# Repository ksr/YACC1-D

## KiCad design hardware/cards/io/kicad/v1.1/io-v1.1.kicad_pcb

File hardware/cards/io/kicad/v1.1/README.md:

# io-v1.1 — KiCad conversion

Generated 2026-09-23 by `tools/eagle_to_kicad_all.py` from the Eagle design `IO V1.1` in `hardware/cards/io/eagle/v1.1/`. **The Eagle files are the record of what was designed and built; this KiCad project is derived from them and is regenerated from scratch on every run of the tool** (hand edits here will be lost - once a card is edited in KiCad, remove it from the tool's list). This revision was FABRICATED (see `hardware/FABRICATED.md`).

## Files

| File | What it is |
|---|---|
| `io-v1.1.kicad_pro` | project; OSH Park rules (6 mil track, 5 mil clearance, 10 mil drill, 4 mil annular) |
| `io-v1.1.kicad_sch` | root sheet; 6 sub-sheet(s) `io-v1.1-sheetN.kicad_sch` mirror the Eagle sheets |
| `io-v1.1-eagle.kicad_sym` | project symbol library generated from the Eagle libraries used (units = Eagle gates) |
| `io-v1.1.kicad_pcb` | the board: 2 copper layers, 71 footprints, 1409 track segments, 158 vias |
| `io-v1.1-eagle.pretty/` | project footprint library extracted from the imported board |
| `reports/` | ERC (`erc.json`), DRC (`drc.json`), schematic PDF, board renders (`-top.png`, `-bottom.png`), netlist + `netlist-compare.txt` |

## Proof

Schematic-vs-board netlist comparison (`tools/kicad/compare_netlists.py`: every (reference, pad) partition must be identical): **MATCH (104/104 nets)**

```
  same connectivity, different net name: [('/Sheet 2/ICLK', 'ICLK'), ('/Sheet 2/RX', 'RX'), ('/Sheet 2/RX-IN', 'RX-IN'), ('/Sheet 2/TX-OUT', 'TX-OUT'), ('/Sheet 5/-IO-ADDRSEL', '-IO-ADDRSEL'), ('/Sheet 5/-IO-DATASEL', '-IO-DATASEL'), ('/Sheet 5/-IO-SEL0', '-IO-SEL0'), ('/Sheet 5/-IO-SEL1', '-IO-SEL1'), ('/Sheet 5/-IO-SEL2', '-IO-SEL2'), ('/Sheet 5/-IO-SEL3', '-IO-SEL3'), ('/Sheet 5/-IO-SEL4', '-IO-SEL4'), ('/Sheet 5/-IO-SEL5', '-IO-SEL5'), ('/Sheet 5/-IO-SEL6', '-IO-SEL6'), ('/Sheet 5/-IO-SEL7', '-IO-SEL7'), ('Net-(HI0A-D0)', 'N$70'), ('Net-(HI0A-D1)', 'N$69'), ('Net-(HI0A-D2)', 'N$68'), ('Net-(HI0A-D3)', 'N$28'), ('Net-(IC1-INT)', 'N$57'), ('Net-(IC1-TX)', 'N$37'), ('Net-(IC1-XTAL1)', 'N$31'), ('Net-(IC2-C1+)', 'N$63'), ('Net-(IC2-C1-)', 'N$62'), ('Net-(IC2-C2+)', 'N$52'), ('Net-(IC2-C2-)', 'N$51'), ('Net-(IC2-V+)', 'N$64'), ('Net-(IC2-V-)', 'N$65'), ('Net-(IC3A-A1)', 'N$1'), ('Net-(IC3A-A2)', 'N$2'), ('Net-(IC3A-A3)', 'N$3'), ('Net-(IC3A-A4)', 'N$4'), ('Net-(IC3A-G)', 'N$32'), ('Net-(IC3B-A1)', 'N$5'), ('Net-(IC3B-A2)', 'N$6'), ('Net-(IC3B-A3)', 'N$7'), ('Net-(IC3B-A4)', 'N$8'), ('Net-(IC4-CLK)', 'N$41'), ('Net-(IC4-Q1)', 'N$26'), ('Net-(IC4-Q2)', 'N$25'), ('Net-(IC4-Q3)', 'N$24'), ('Net-(IC4-Q4)', 'N$23'), ('Net-(IC4-Q5)', 'N$22'), ('Net-(IC4-Q6)', 'N$21'), ('Net-(IC4-Q7)', 'N$20'), ('Net-(IC4-Q8)', 'N$19'), ('Net-(IC5-G1)', 'N$29'), ('Net-(IC5-G2A)', 'N$27'), ('Net-(IC6C-O)', 'N$33'), ('Net-(IC7A-O)', 'N$30'), ('Net-(IC7B-I0)', 'N$67'), ('Net-(IC8F-I)', 'N$66'), ('Net-(IC9-Q1)', 'N$74'), ('Net-(IC9-Q2)', 'N$73'), ('Net-(IC9-Q3)', 'N$72'), ('Net-(IC9-Q4)', 'N$71'), ('Net-(IC10-CLK)', 'N$40'), ('Net-(IC11A-O)', 'N$75'), ('Net-(IN0-P)', 'N$34'), ('Net-(J1-Pad2)', 'N$35'), ('Net-(J1-Pad3)', 'N$36'), ('Net-(OUT0-PadA)', 'N$9'), ('Net-(PWR0-PadA)', 'N$11'), ('Net-(R3-Pad1)', 'N$14'), ('Net-(R4-Pad1)', 'N$15'), ('Net-(R5-Pad1)', 'N$10'), ('Net-(R6-Pad1)', 'N$12'), ('Net-(R7-Pad1)', 'N$13'), ('Net-(R8-Pad1)', 'N$16'), ('Net-(R9-Pad1)', 'N$18'), ('Net-(R10-Pad1)', 'N$17'), ('Net-(TM1-S)', 'N$44')]
```

## Readability

`tools/kicad/sch_overlaps.py` over every sheet: text over text 13, text over a symbol body 57, text crossed by a line 22, items off the drawing frame or on the title block 0. What is left is mostly the Eagle drawing itself (parts placed that close in Eagle) or KiCad drawing pin numbers centred on short pins.

## Residual ERC / DRC

ERC by type: endpoint_off_grid 38, isolated_pin_label 66, pin_not_connected 8, pin_not_driven 1, unconnected_wire_endpoint 17.
`isolated_pin_label` = the converter's per-net global labels (cosmetic); `power_pin_not_driven` / unused-unit notes are the same ones KiCad's own Eagle importer leaves. `unconnected_wire_endpoint` / `pin_not_connected` = wire stubs Eagle leaves bare (mostly net wires ending on a bus, which is drawn as graphics here); since 2026-09-23 the converter no longer hangs a label on every such end (that was most of the label clutter), so they show as KiCad warnings.

DRC by type: items_not_allowed 22, lib_footprint_mismatch 2, silk_edge_clearance 4, silk_over_copper 199, silk_overlap 60, text_height 4, text_thickness 1; unconnected items 0; schematic parity 0.
Silk-over-pad and clearance notes reflect the Eagle design as drawn; unconnected items are Eagle airwires (parts the design left unrouted).

Converter: converted: 214 symbols, 595 wires, 204 labels, 103 junctions, 8 bus lines, 17 no-connects

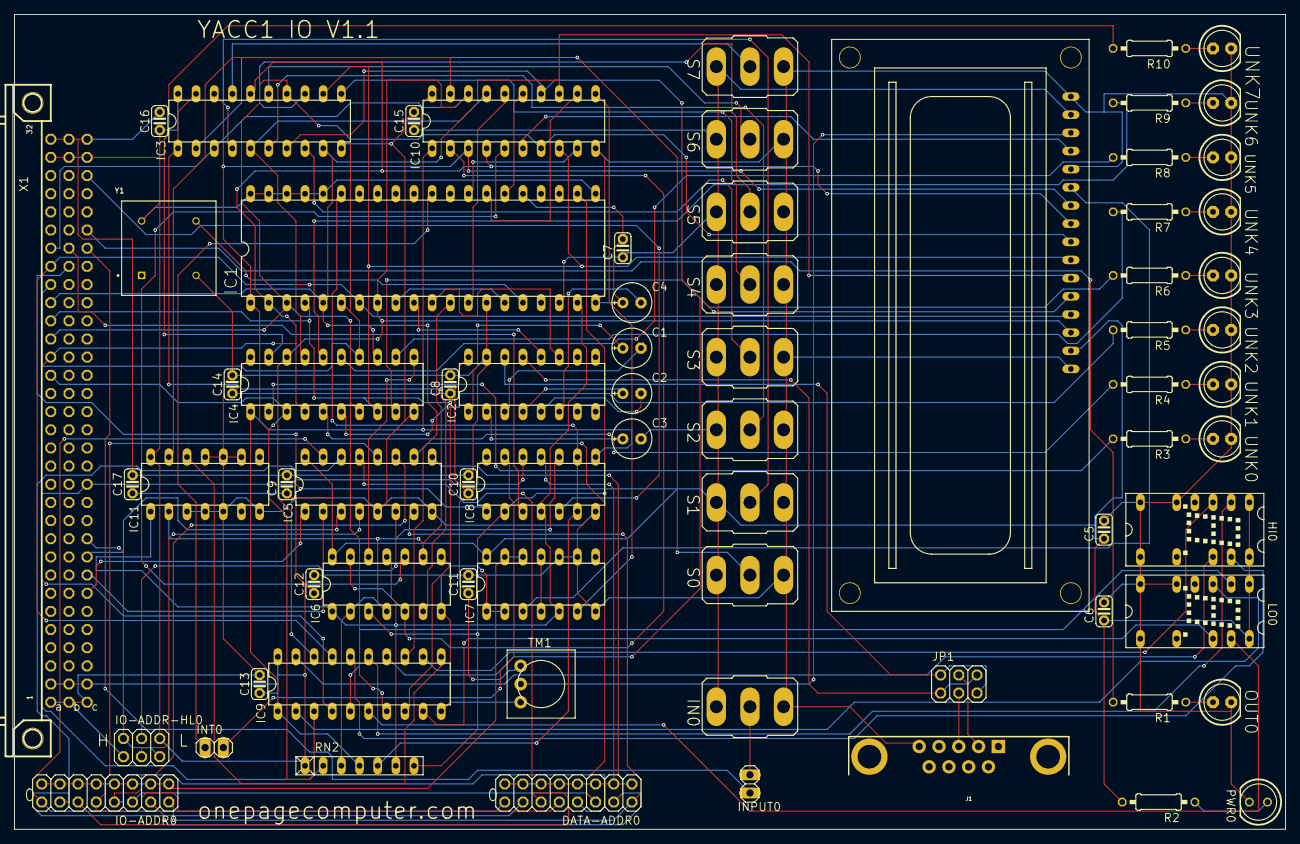
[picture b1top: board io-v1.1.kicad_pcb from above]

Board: 2 copper layers, 177.8 x 114.0 mm, 71 parts (0 on the bottom side), 104 nets.

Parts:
C1, C2, C3, C4: E2,5-6E
C5, C6, C7, C8, C9, C10, C11, C12, C13, C14, C15, C16, C17: C025-024X044
DATA-ADDR0: 2X08
HI0: HTIL311A
IC1: DIL40
IC2: MAX232; DIL16
IC3: 74LS244N; DIL20
IC4, IC9, IC10: 74273N; DIL20
IC5: 74LS138N; DIL16
IC6, IC11: 74LS10N; DIL14
IC7: 74LS00N; DIL14
IC8: 74LS06N; DIL14
IN0: M9040P
INPUT0: 1X02
INT0: 1X02
IO-ADDR0: 2X08
IO-ADDR-HL0: 2X03
J1: DB9
JP1: PINHD-2X3; 2X03
LO0: HTIL311A
OUT0: LED5MM
PWR0: LED5MM
R1, R3, R4, R5, R6, R7, R8, R9, R10: 0207_10
R2: 330; 0207_10
RN2: RN-7
S0, S1, S2, S3, S4, S5, S6, S7: M9040P
TM1: 10k; TRIM-3386
UNK0, UNK1, UNK2, UNK3, UNK4, UNK5, UNK6, UNK7: LED5MM
X1: FABC96R
X2: HD44780LCD-1602; LCD1602
Y1: ECS-2100AX-200

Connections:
-B-RESET: IC4.1, IC8.8, IC9.1, IC10.1, RN2.4
-INT: IC8.12, RN2.2, X1.C13
-IO-ADDRSEL: IC7.12, IC7.13, IO-ADDR0.1, IO-ADDR0.3, IO-ADDR0.5, IO-ADDR0.7, IO-ADDR0.9, IO-ADDR0.11, IO-ADDR0.13, IO-ADDR0.15
-IO-DATASEL: DATA-ADDR0.1, DATA-ADDR0.3, DATA-ADDR0.5, DATA-ADDR0.7, DATA-ADDR0.9, DATA-ADDR0.11, DATA-ADDR0.13, DATA-ADDR0.15, IC8.11
-IO-RD: IC8.1, X1.B25
-IO-SEL0: DATA-ADDR0.16, IC5.15, IO-ADDR0.16
-IO-SEL1: DATA-ADDR0.14, IC5.14, IO-ADDR0.14
-IO-SEL2: DATA-ADDR0.12, IC5.13, IO-ADDR0.12
-IO-SEL3: DATA-ADDR0.10, IC5.12, IO-ADDR0.10
-IO-SEL4: DATA-ADDR0.8, IC5.11, IO-ADDR0.8
-IO-SEL5: DATA-ADDR0.6, IC5.10, IO-ADDR0.6
-IO-SEL6: DATA-ADDR0.4, IC5.9, IO-ADDR0.4
-IO-SEL7: DATA-ADDR0.2, IC5.7, IO-ADDR0.2
-IO-WR: IC8.3, X1.B26
-RESET: IC8.5, X1.C30
DATA0: IC1.1, IC3.18, IC4.3, IC9.3, IC10.3, X1.A19, X2.7
DATA1: IC1.2, IC3.16, IC4.4, IC9.4, IC10.4, X1.A20, X2.8
DATA2: IC1.3, IC3.14, IC4.7, IC9.7, IC10.7, X1.A21, X2.9
DATA3: IC1.4, IC3.12, IC4.8, IC9.8, IC10.8, X1.A22, X2.10
DATA4: IC1.5, IC3.9, IC4.13, IC9.13, IC10.13, X1.A23, X2.11
DATA5: IC1.6, IC3.7, IC4.14, IC9.14, IC10.14, X1.A24, X2.12
DATA6: IC1.7, IC3.5, IC4.17, IC9.17, IC10.17, X1.A25, X2.13
DATA7: IC1.8, IC3.3, IC4.18, IC9.18, IC10.18, X1.A26, X2.14
GND: C4.+, C5.2, C6.2, C7.2, C8.2, C9.2, C10.2, C11.2, C12.2, C13.2, C14.2, C15.2, C16.2, C17.2, HI0.5, HI0.7, HI0.8, IC1.14, IC1.20, IC1.25, IC2.15, IC3.10, IC4.10, IC5.5, IC5.8, IC6.7, IC7.7, IC7.9, IC7.10, IC8.7, IC9.10, IC10.10, IC11.3, IC11.4, IC11.5, IC11.7, IC11.9, IC11.10, IC11.11, IN0.3, IO-ADDR-HL0.1, J1.5, LO0.5, LO0.7, LO0.8, OUT0.K, PWR0.K, S0.3, S1.3, S2.3, S3.3, S4.3, S5.3, S6.3, S7.3, TM1.3, UNK0.K, UNK1.K, UNK2.K, UNK3.K, UNK4.K, UNK5.K, UNK6.K, UNK7.K, X1.A1, X1.A32, X1.B1, X1.B32, X1.C1, X1.C32, X2.1, X2.5, X2.16, Y1.4
ICLK: IC1.9, IC1.15
IN: INPUT0.1, X1.C26
IO-ADDR0: IC5.1, X1.C7
IO-ADDR1: IC5.2, X1.C8
IO-ADDR2: IC5.3, X1.C9
IO-ADDR3: IO-ADDR-HL0.2, IO-ADDR-HL0.5, X1.C10
IO-RD: IC1.22, IC6.3, IC8.2, RN2.7
IO-SELDATA: IC1.12, IC6.2, IC6.4, IC6.9, IC8.10, IC11.2, RN2.3
IO-WR: IC1.19, IC6.1, IC6.11, IC7.5, IC8.4, IC11.1, RN2.6
LCD-ENABLE: IC6.10, IC10.5
LCD-REGISTER: IC10.6, X2.4
unnamed: IC3.2, S0.2
unnamed: IC3.4, S1.2
unnamed: IC3.6, S2.2
unnamed: IC3.8, S3.2
unnamed: IC3.11, S4.2
unnamed: IC3.13, S5.2
unnamed: IC3.15, S6.2
unnamed: IC3.17, S7.2
unnamed: OUT0.A, R1.1
unnamed: R5.1, UNK2.A
unnamed: PWR0.A, R2.1
unnamed: R6.1, UNK3.A
unnamed: R7.1, UNK4.A
unnamed: R3.1, UNK0.A
unnamed: R4.1, UNK1.A
unnamed: R8.1, UNK5.A
unnamed: R10.1, UNK7.A
unnamed: R9.1, UNK6.A
unnamed: IC4.19, R10.2
unnamed: IC4.16, R9.2
unnamed: IC4.15, R8.2
unnamed: IC4.12, R7.2
unnamed: IC4.9, R6.2
unnamed: IC4.6, R5.2
unnamed: IC4.5, R4.2
unnamed: IC4.2, R3.2
unnamed: IC5.4, IO-ADDR-HL0.3
unnamed: HI0.12, IC9.19
unnamed: IC5.6, IO-ADDR-HL0.4
unnamed: IC7.3, X2.6
unnamed: IC1.16, Y1.5
unnamed: IC3.1, IC3.19, IC6.6
unnamed: IC6.8, IC7.1, IC7.2
unnamed: IN0.2, INPUT0.2
unnamed: J1.2, JP1.4
unnamed: J1.3, JP1.3
unnamed: IC1.11, IC2.11
unnamed: IC7.6, IC10.11
unnamed: IC4.11, IC6.12
unnamed: TM1.2, X2.3
unnamed: C2.-, IC2.5
unnamed: C2.+, IC2.4
unnamed: IC1.30, INT0.1
unnamed: C1.-, IC2.3
unnamed: C1.+, IC2.1
unnamed: C3.+, IC2.2
unnamed: C4.-, IC2.6
unnamed: IC8.13, INT0.2
unnamed: IC7.4, IC7.11
unnamed: HI0.13, IC9.16
unnamed: HI0.2, IC9.15
unnamed: HI0.3, IC9.12
unnamed: IC9.9, LO0.12
unnamed: IC9.6, LO0.13
unnamed: IC9.5, LO0.2
unnamed: IC9.2, LO0.3
unnamed: IC9.11, IC11.12
OUT: R1.2, X1.C27
RESET: IC1.35, IC8.6, IC8.9, RN2.5
RX: IC1.10, IC2.12
RX-IN: IC2.13, JP1.1, JP1.6
SWITCH-LED: IC6.5, IC6.13, IC10.2
TIL311: IC10.19, IC11.13
TX-OUT: IC2.14, JP1.2, JP1.5
UART-A0: IC1.28, IC10.9
UART-A1: IC1.27, IC10.12
UART-A2: IC1.26, IC10.15
UART-CS: IC1.13, IC10.16
VCC: C3.-, C5.1, C6.1, C7.1, C8.1, C9.1, C10.1, C11.1, C12.1, C13.1, C14.1, C15.1, C16.1, C17.1, HI0.1, HI0.14, IC1.18, IC1.21, IC1.36, IC1.37, IC1.38, IC1.39, IC1.40, IC2.16, IC3.20, IC4.20, IC5.16, IC6.14, IC7.14, IC8.14, IC9.20, IC10.20, IC11.14, IN0.1, IO-ADDR-HL0.6, LO0.1, LO0.14, R2.2, RN2.1, S0.1, S1.1, S2.1, S3.1, S4.1, S5.1, S6.1, S7.1, TM1.1, X1.A2, X1.A31, X1.B2, X1.B31, X1.C2, X1.C31, X2.2, X2.15, Y1.8

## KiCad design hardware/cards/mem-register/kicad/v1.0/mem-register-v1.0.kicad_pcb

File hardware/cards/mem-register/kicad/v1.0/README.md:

# mem-register-v1.0 — KiCad conversion

Generated 2026-09-23 by `tools/eagle_to_kicad_all.py` from the Eagle design `Mem Register V1.0` in `hardware/cards/mem-register/eagle/v1.0/`. **The Eagle files are the record of what was designed and built; this KiCad project is derived from them and is regenerated from scratch on every run of the tool** (hand edits here will be lost - once a card is edited in KiCad, remove it from the tool's list). This revision was FABRICATED (see `hardware/FABRICATED.md`).

## Files

| File | What it is |
|---|---|
| `mem-register-v1.0.kicad_pro` | project; OSH Park rules (6 mil track, 5 mil clearance, 10 mil drill, 4 mil annular) |
| `mem-register-v1.0.kicad_sch` | root sheet; 3 sub-sheet(s) `mem-register-v1.0-sheetN.kicad_sch` mirror the Eagle sheets |
| `mem-register-v1.0-eagle.kicad_sym` | project symbol library generated from the Eagle libraries used (units = Eagle gates) |
| `mem-register-v1.0.kicad_pcb` | the board: 2 copper layers, 90 footprints, 1651 track segments, 107 vias |
| `mem-register-v1.0-eagle.pretty/` | project footprint library extracted from the imported board |
| `reports/` | ERC (`erc.json`), DRC (`drc.json`), schematic PDF, board renders (`-top.png`, `-bottom.png`), netlist + `netlist-compare.txt` |

## Proof

Schematic-vs-board netlist comparison (`tools/kicad/compare_netlists.py`: every (reference, pad) partition must be identical): **MATCH (107/107 nets)**

```
  same connectivity, different net name: [('Net-(IC1A-O)', 'N$19'), ('Net-(IC1B-O)', 'N$37'), ('Net-(IC1C-O)', 'N$82'), ('Net-(IC2-G1)', 'N$6'), ('Net-(IC4-A=B_I)', 'N$8'), ('Net-(IC4-B0)', 'N$28'), ('Net-(IC4-B1)', 'N$46'), ('Net-(IC4-B2)', 'N$64'), ('Net-(IC4-B3)', 'N$73'), ('Net-(IC5-G2A)', 'N$4'), ('Net-(IC6-G2B)', 'N$3'), ('Net-(IC7A-O)', 'N$2'), ('Net-(PWR0-PadA)', 'N$11'), ('Net-(RD1-PadA)', 'N$1'), ('Net-(RD2-PadA)', 'N$7'), ('Net-(RD3-PadA)', 'N$5'), ('Net-(RD4-PadA)', 'N$10'), ('Net-(RD5-PadA)', 'N$12'), ('Net-(RD6-PadA)', 'N$15'), ('Net-(RD7-PadA)', 'N$13'), ('Net-(RD8-PadA)', 'N$14'), ('Net-(RD9-PadA)', 'N$9'), ('Net-(RD10-PadA)', 'N$16'), ('Net-(RD11-PadA)', 'N$17'), ('Net-(RD12-PadA)', 'N$18'), ('Net-(RD13-PadA)', 'N$20'), ('Net-(RD14-PadA)', 'N$21'), ('Net-(RD15-PadA)', 'N$22'), ('Net-(RD16-PadA)', 'N$23'), ('Net-(RN3-Pad2)', 'N$24'), ('Net-(RN3-Pad3)', 'N$25'), ('Net-(RN3-Pad4)', 'N$26'), ('Net-(RN3-Pad5)', 'N$27'), ('Net-(RN3-Pad6)', 'N$30'), ('Net-(RN3-Pad7)', 'N$29'), ('Net-(RN3-Pad8)', 'N$31'), ('Net-(RN3-Pad9)', 'N$32'), ('Net-(RN5-Pad2)', 'N$33'), ('Net-(RN5-Pad3)', 'N$41'), ('Net-(RN5-Pad4)', 'N$34'), ('Net-(RN5-Pad5)', 'N$40'), ('Net-(RN5-Pad6)', 'N$35'), ('Net-(RN5-Pad7)', 'N$39'), ('Net-(RN5-Pad8)', 'N$36'), ('Net-(RN5-Pad9)', 'N$38')]
```

## Readability

`tools/kicad/sch_overlaps.py` over every sheet: text over text 4, text over a symbol body 77, text crossed by a line 90, items off the drawing frame or on the title block 0. What is left is mostly the Eagle drawing itself (parts placed that close in Eagle) or KiCad drawing pin numbers centred on short pins.

## Residual ERC / DRC

ERC by type: endpoint_off_grid 27, isolated_pin_label 56, unconnected_wire_endpoint 96.
`isolated_pin_label` = the converter's per-net global labels (cosmetic); `power_pin_not_driven` / unused-unit notes are the same ones KiCad's own Eagle importer leaves. `unconnected_wire_endpoint` / `pin_not_connected` = wire stubs Eagle leaves bare (mostly net wires ending on a bus, which is drawn as graphics here); since 2026-09-23 the converter no longer hangs a label on every such end (that was most of the label clutter), so they show as KiCad warnings.

DRC by type: items_not_allowed 2, lib_footprint_mismatch 1, silk_edge_clearance 4, silk_over_copper 199, silk_overlap 91, text_height 2; unconnected items 0; schematic parity 0.
Silk-over-pad and clearance notes reflect the Eagle design as drawn; unconnected items are Eagle airwires (parts the design left unrouted).

Converter: converted: 203 symbols, 664 wires, 430 labels, 83 junctions, 33 bus lines, 3 no-connects

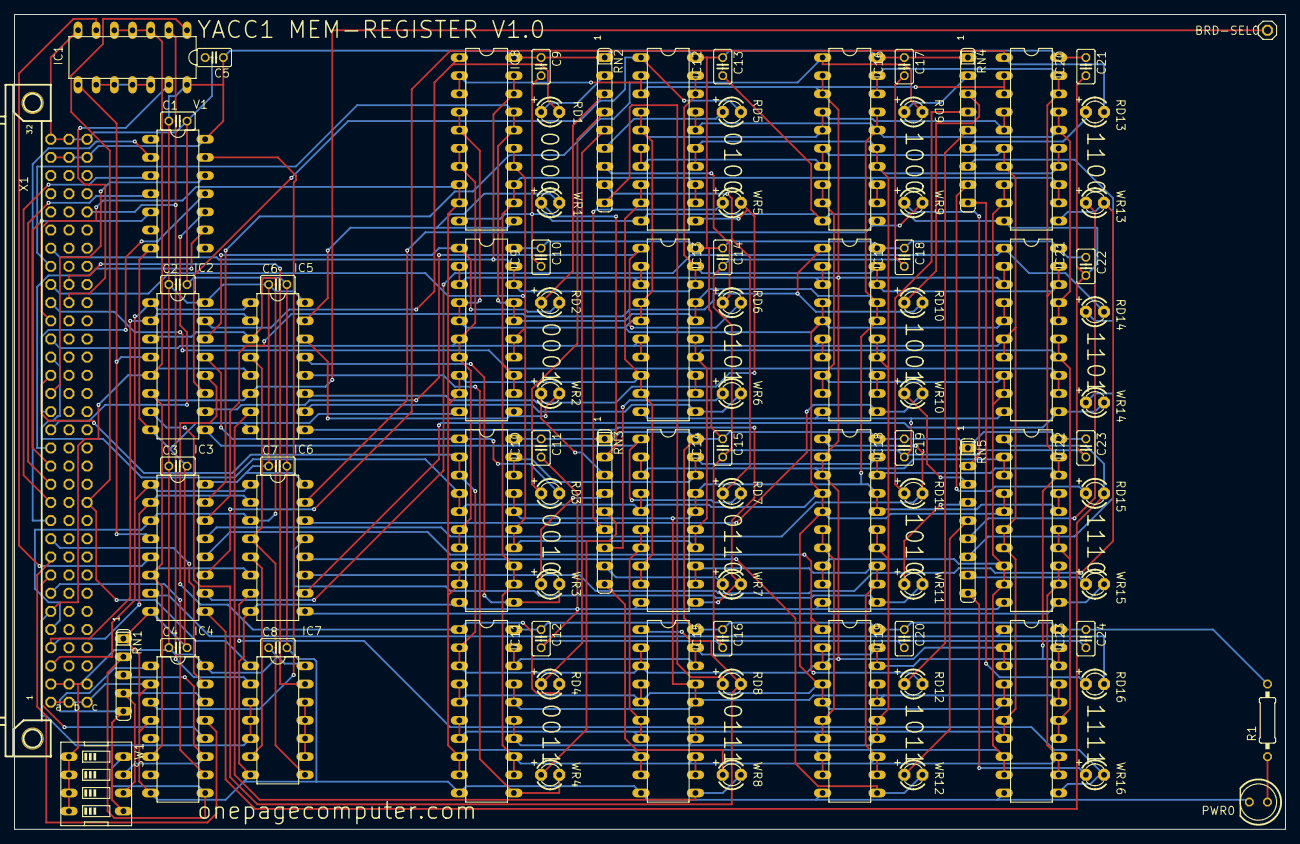
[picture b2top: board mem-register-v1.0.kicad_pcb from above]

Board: 2 copper layers, 177.8 x 114.0 mm, 90 parts (0 on the bottom side), 107 nets.

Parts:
BRD-SEL0: PINHD-1X1; 1X01
C1, C2, C3, C4, C5, C6, C7, C8, C9, C10, C11, C12, C13, C14, C15, C16, C17, C18, C19, C20, C21, C22, C23, C24: C025-025X050
IC1, IC7: 74ALS27N; DIL14
IC2, IC3, IC5, IC6: 74LS138N; DIL16
IC4: 74LS85N; DIL16
IC8, IC9, IC10, IC11, IC12, IC13, IC14, IC15, IC16, IC17, IC18, IC19, IC20, IC21, IC22, IC23: 74LS374N; DIL20
PWR0: LED5MM
R1: 330; 0207_10
RD1, RD2, RD3, RD4, RD5, RD6, RD7, RD8, RD9, RD10, RD11, RD12, RD13, RD14, RD15, RD16: LED3MM
RN1: SIL5
RN2, RN3, RN4, RN5: SIL9
SW1: EDG-04
V1: 744078N; DIL14
WR1, WR2, WR3, WR4, WR5, WR6, WR7, WR8, WR9, WR10, WR11, WR12, WR13, WR14, WR15, WR16: LED3MM
X1: FABC96R

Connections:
-BUS-EN: IC1.2, IC7.2, X1.C28
-MEM-RD: IC1.13, X1.B23
-MEM-WR: IC7.13, X1.B24
-VMA: IC1.1, IC7.1, X1.C12
ADDR0: IC2.1, IC3.1, IC5.1, IC6.1, X1.A3
ADDR1: IC2.2, IC3.2, IC5.2, IC6.2, X1.A4
ADDR2: IC2.3, IC3.3, IC5.3, IC6.3, X1.A5
ADDR3: IC1.3, IC1.4, IC1.5, IC2.5, IC5.5, IC7.3, IC7.4, IC7.5, X1.A6
ADDR4: IC4.10, X1.A7
ADDR5: IC4.12, X1.A8
ADDR6: IC4.13, X1.A9
ADDR7: IC4.15, X1.A10
ADDR8: V1.2, X1.A11
ADDR9: V1.3, X1.A12
ADDR10: V1.4, X1.A13
ADDR11: V1.5, X1.A14
ADDR12: V1.9, X1.A15
ADDR13: V1.10, X1.A16
ADDR14: V1.11, X1.A17
ADDR15: V1.12, X1.A18
DATA0: IC8.2, IC8.3, IC9.2, IC9.3, IC10.2, IC10.3, IC11.2, IC11.3, IC12.2, IC12.3, IC13.2, IC13.3, IC14.2, IC14.3, IC15.2, IC15.3, IC16.2, IC16.3, IC17.2, IC17.3, IC18.2, IC18.3, IC19.2, IC19.3, IC20.2, IC20.3, IC21.2, IC21.3, IC22.2, IC22.3, IC23.2, IC23.3, X1.A19
DATA1: IC8.4, IC8.5, IC9.4, IC9.5, IC10.4, IC10.5, IC11.4, IC11.5, IC12.4, IC12.5, IC13.4, IC13.5, IC14.4, IC14.5, IC15.4, IC15.5, IC16.4, IC16.5, IC17.4, IC17.5, IC18.4, IC18.5, IC19.4, IC19.5, IC20.4, IC20.5, IC21.4, IC21.5, IC22.4, IC22.5, IC23.4, IC23.5, X1.A20
DATA2: IC8.6, IC8.7, IC9.6, IC9.7, IC10.6, IC10.7, IC11.6, IC11.7, IC12.6, IC12.7, IC13.6, IC13.7, IC14.6, IC14.7, IC15.6, IC15.7, IC16.6, IC16.7, IC17.6, IC17.7, IC18.6, IC18.7, IC19.6, IC19.7, IC20.6, IC20.7, IC21.6, IC21.7, IC22.6, IC22.7, IC23.6, IC23.7, X1.A21
DATA3: IC8.8, IC8.9, IC9.8, IC9.9, IC10.8, IC10.9, IC11.8, IC11.9, IC12.8, IC12.9, IC13.8, IC13.9, IC14.8, IC14.9, IC15.8, IC15.9, IC16.8, IC16.9, IC17.8, IC17.9, IC18.8, IC18.9, IC19.8, IC19.9, IC20.8, IC20.9, IC21.8, IC21.9, IC22.8, IC22.9, IC23.8, IC23.9, X1.A22
DATA4: IC8.12, IC8.13, IC9.12, IC9.13, IC10.12, IC10.13, IC11.12, IC11.13, IC12.12, IC12.13, IC13.12, IC13.13, IC14.12, IC14.13, IC15.12, IC15.13, IC16.12, IC16.13, IC17.12, IC17.13, IC18.12, IC18.13, IC19.12, IC19.13, IC20.12, IC20.13, IC21.12, IC21.13, IC22.12, IC22.13, IC23.12, IC23.13, X1.A23
DATA5: IC8.14, IC8.15, IC9.14, IC9.15, IC10.14, IC10.15, IC11.14, IC11.15, IC12.14, IC12.15, IC13.14, IC13.15, IC14.14, IC14.15, IC15.14, IC15.15, IC16.14, IC16.15, IC17.14, IC17.15, IC18.14, IC18.15, IC19.14, IC19.15, IC20.14, IC20.15, IC21.14, IC21.15, IC22.14, IC22.15, IC23.14, IC23.15, X1.A24
DATA6: IC8.16, IC8.17, IC9.16, IC9.17, IC10.16, IC10.17, IC11.16, IC11.17, IC12.16, IC12.17, IC13.16, IC13.17, IC14.16, IC14.17, IC15.16, IC15.17, IC16.16, IC16.17, IC17.16, IC17.17, IC18.16, IC18.17, IC19.16, IC19.17, IC20.16, IC20.17, IC21.16, IC21.17, IC22.16, IC22.17, IC23.16, IC23.17, X1.A25
DATA7: IC8.18, IC8.19, IC9.18, IC9.19, IC10.18, IC10.19, IC11.18, IC11.19, IC12.18, IC12.19, IC13.18, IC13.19, IC14.18, IC14.19, IC15.18, IC15.19, IC16.18, IC16.19, IC17.18, IC17.19, IC18.18, IC18.19, IC19.18, IC19.19, IC20.18, IC20.19, IC21.18, IC21.19, IC22.18, IC22.19, IC23.18, IC23.19, X1.A26
GND: C1.2, C2.2, C3.2, C4.2, C5.2, C6.2, C7.2, C8.2, C9.2, C10.2, C11.2, C12.2, C13.2, C14.2, C15.2, C16.2, C17.2, C18.2, C19.2, C20.2, C21.2, C22.2, C23.2, C24.2, IC1.7, IC2.8, IC3.8, IC4.2, IC4.4, IC4.8, IC5.8, IC6.8, IC7.7, IC8.10, IC9.10, IC10.10, IC11.10, IC12.10, IC13.10, IC14.10, IC15.10, IC16.10, IC17.10, IC18.10, IC19.10, IC20.10, IC21.10, IC22.10, IC23.10, PWR0.K, RN1.1, V1.7, X1.A1, X1.A32, X1.B1, X1.B32, X1.C1, X1.C32
unnamed: RD1.A, RN2.2
unnamed: IC7.9, IC7.10, IC7.11, IC7.12
unnamed: IC6.5, IC7.6
unnamed: IC5.4, IC6.4, IC7.8
unnamed: RD3.A, RN2.4
unnamed: BRD-SEL0.1, IC2.6, IC3.6, IC4.6, IC5.6, IC6.6
unnamed: RD2.A, RN2.3
unnamed: IC4.3, V1.13
unnamed: RD9.A, RN4.2
unnamed: RD4.A, RN2.5
unnamed: PWR0.A, R1.1
unnamed: RD5.A, RN2.6
unnamed: RD7.A, RN2.8
unnamed: RD8.A, RN2.9
unnamed: RD6.A, RN2.7
unnamed: RD10.A, RN4.3
unnamed: RD11.A, RN4.4
unnamed: RD12.A, RN4.5
unnamed: IC1.9, IC1.10, IC1.11, IC1.12
unnamed: RD13.A, RN4.6
unnamed: RD14.A, RN4.7
unnamed: RD15.A, RN4.8
unnamed: RD16.A, RN4.9
unnamed: RN3.2, WR1.A
unnamed: RN3.3, WR2.A
unnamed: RN3.4, WR3.A
unnamed: RN3.5, WR4.A
unnamed: IC4.9, RN1.2, SW1.8
unnamed: RN3.7, WR6.A
unnamed: RN3.6, WR5.A
unnamed: RN3.8, WR7.A
unnamed: RN3.9, WR8.A
unnamed: RN5.2, WR9.A
unnamed: RN5.4, WR11.A
unnamed: RN5.6, WR13.A
unnamed: RN5.8, WR15.A
unnamed: IC1.6, IC3.5
unnamed: RN5.9, WR16.A
unnamed: RN5.7, WR14.A
unnamed: RN5.5, WR12.A
unnamed: RN5.3, WR10.A
unnamed: IC4.11, RN1.3, SW1.7
unnamed: IC4.14, RN1.4, SW1.6
unnamed: IC4.1, RN1.5, SW1.5
unnamed: IC1.8, IC2.4, IC3.4
RD0: IC2.15, IC8.1, RD1.K
RD1: IC2.14, IC9.1, RD2.K
RD2: IC2.13, IC10.1, RD3.K
RD3: IC2.12, IC11.1, RD4.K
RD4: IC2.11, IC12.1, RD5.K
RD5: IC2.10, IC13.1, RD6.K
RD6: IC2.9, IC14.1, RD7.K
RD7: IC2.7, IC15.1, RD8.K
RD8: IC3.15, IC16.1, RD9.K
RD9: IC3.14, IC17.1, RD10.K
RD10: IC3.13, IC18.1, RD11.K
RD11: IC3.12, IC19.1, RD12.K
RD12: IC3.11, IC20.1, RD13.K
RD13: IC3.10, IC21.1, RD14.K
RD14: IC3.9, IC22.1, RD15.K
RD15: IC3.7, IC23.1, RD16.K
VCC: C1.1, C2.1, C3.1, C4.1, C5.1, C6.1, C7.1, C8.1, C9.1, C10.1, C11.1, C12.1, C13.1, C14.1, C15.1, C16.1, C17.1, C18.1, C19.1, C20.1, C21.1, C22.1, C23.1, C24.1, IC1.14, IC2.16, IC3.16, IC4.16, IC5.16, IC6.16, IC7.14, IC8.20, IC9.20, IC10.20, IC11.20, IC12.20, IC13.20, IC14.20, IC15.20, IC16.20, IC17.20, IC18.20, IC19.20, IC20.20, IC21.20, IC22.20, IC23.20, R1.2, RN2.1, RN3.1, RN4.1, RN5.1, SW1.1, SW1.2, SW1.3, SW1.4, V1.14, X1.A2, X1.A31, X1.B2, X1.B31, X1.C2, X1.C31
WR0: IC5.15, IC8.11, WR1.K
WR1: IC5.14, IC9.11, WR2.K
WR2: IC5.13, IC10.11, WR3.K
WR3: IC5.12, IC11.11, WR4.K
WR4: IC5.11, IC12.11, WR5.K
WR5: IC5.10, IC13.11, WR6.K
WR6: IC5.9, IC14.11, WR7.K
WR7: IC5.7, IC15.11, WR8.K
WR8: IC6.15, IC16.11, WR9.K
WR9: IC6.14, IC17.11, WR10.K
WR10: IC6.13, IC18.11, WR11.K
WR11: IC6.12, IC19.11, WR12.K
WR12: IC6.11, IC20.11, WR13.K
WR13: IC6.10, IC21.11, WR14.K
WR14: IC6.9, IC22.11, WR15.K
WR15: IC6.7, IC23.11, WR16.K

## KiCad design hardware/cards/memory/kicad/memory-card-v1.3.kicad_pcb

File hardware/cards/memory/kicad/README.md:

# YACC1 Memory Card v1.3 — KiCad conversion

Converted 2026-09-19 from the Eagle 9.7 design in
`YACCS/YACC gitversion/YACC1-2020/PCB/Working - Under Develolpment/Memory v1.3/`
(the newest copy of the card anywhere in the YACCS tree). **No Eagle file was modified.**
Byte-identical copies of the sources are in `eagle-source/`.

This is the pilot for moving the whole YACC1 design set off Eagle. It is the v1.3 card that
is in the machine today: 2 x 62256 RAM, 1 x 28C64 EEPROM, boot remap of ROM to $0000 until
the first A15 access, and the 3x8 jumper header that maps each 4K block of the upper half
to hi RAM, ROM, or nothing (the $D000 block is left undecoded for the video card).

## Files

| File | What it is |
|---|---|
| `memory-card-v1.3.kicad_pro` | project; OSH Park 4-layer rules (6 mil track, 5 mil clearance, 10 mil drill, 4 mil annular) |
| `memory-card-v1.3.kicad_sch` | root sheet; six sub-sheets `memory-card-v1.3-sheet1..6.kicad_sch` mirror the six Eagle sheets |
| `memory-card-v1.3.kicad_pcb` | the board, imported with `kicad-cli pcb import`, then finished (see below) |
| `memory-card-v1.3-eagle.kicad_sym` | project symbol library generated from the Eagle libraries used |
| `memory-card-v1.3-eagle.pretty/` | project footprint library extracted from the imported board |
| `sym-lib-table`, `fp-lib-table` | point KiCad at the two project libraries |
| `eagle-source/` | the original `.sch`, `.brd`, `.pro`, `Notes.rtf`, `ROM ZSelect.circ` |
| `reports/` | ERC, DRC, netlist, netlist comparison, schematic PDF, board renders |
| `tools/` | the converter and checkers (re-runnable, deterministic) |

## How it was converted

1. **Board**: `kicad-cli pcb import --format eagle` on the `.brd`. It preserved the 4-layer stack
   (tracks on F.Cu/B.Cu, GND and VCC planes on In1.Cu/In2.Cu), 52 footprints, 968 tracks, 80 vias.
2. **Schematic**: KiCad's Eagle schematic importer is GUI-only, so `tools/eagle_sch_to_kicad.py`
   converts the Eagle XML directly: symbols become a project library (units = Eagle gates),
   unplaced 74xx power gates become hidden power pins as in Eagle, supply symbols become KiCad
   power symbols, every net segment carries a global label with the Eagle net name (Eagle nets are
   global across sheets), buses are drawn as cosmetic lines, unused gate pins get no-connect flags.
3. **Board finishing**: `tools/finish_board.py` (run with KiCad's bundled Python) extracts the
   footprints into `.pretty`, moves a stray dimension line that the bus-connector package had put
   on Edge.Cuts, applies the OSH Park rules, links every footprint to its schematic symbol, and
   refills the two power planes.

## Proof of correctness

`tools/compare_netlists.py` reduces both the KiCad schematic netlist and the pad netlist embedded
in the imported board (i.e. Eagle's own connectivity) to partitions of (reference, pad) and requires
them to be identical. Result: **115 of 115 multi-pin nets identical, no pad differs**
(`reports/netlist-compare.txt`). Two nets that Eagle had left auto-named (N$1, N$14) simply carry
KiCad auto-names.

Re-run any time:

```
python3 tools/eagle_sch_to_kicad.py "eagle-source/Memory V1.3.sch" . memory-card-v1.3
kicad-cli sch export netlist --format kicadsexpr -o reports/netlist.net memory-card-v1.3.kicad_sch
python3 tools/compare_netlists.py reports/netlist.net memory-card-v1.3.kicad_pcb
```

## What the reports still show, and why

- **ERC**: 43 *isolated pin label* warnings (a label sitting directly on a pin, Eagle style),
  hidden-power-pin notes on IC5 and IC14, and *missing unit* / *unused input* on IC14's spare
  gates. All are cosmetic; the netlist proves the connections.
- **DRC**: ~200 *silk over copper* warnings (Eagle silkscreen conventions), and 100 "unconnected"
  items that all belong to IC26–IC29, RN5, RN6, C9 and their nets. Those are the two 16-bit
  temporary registers: they are **unplaced in the Eagle v1.3 layout as well** (parked off the board
  edge with airwires), so KiCad is reporting the same incompleteness Eagle had.
- `PWR` (the power LED) became `PWR0`: KiCad references must end in a digit, and this matches what
  KiCad's own Eagle board importer chose.

## Known design facts verified on hardware (2026-09-18)

Block-select jumpers: up = hi RAM, down = ROM, none = undecoded. Current card: $8000–$CFFF RAM,
$D000 undecoded (reserved for the video card), $E000–$FFFF ROM (the 28C64 is 8K). The EEPROM
holds the Software-vs July-2021 build of monitor + BASIC (git commit ff7d85a).

---
*YACC1-D note (2026-09-20): the `tools/` folder this README mentions is not kept here; the maintained converter, netlist prover and board finisher are in `tools/kicad/` at the repo root (newer than the pilot copies).*

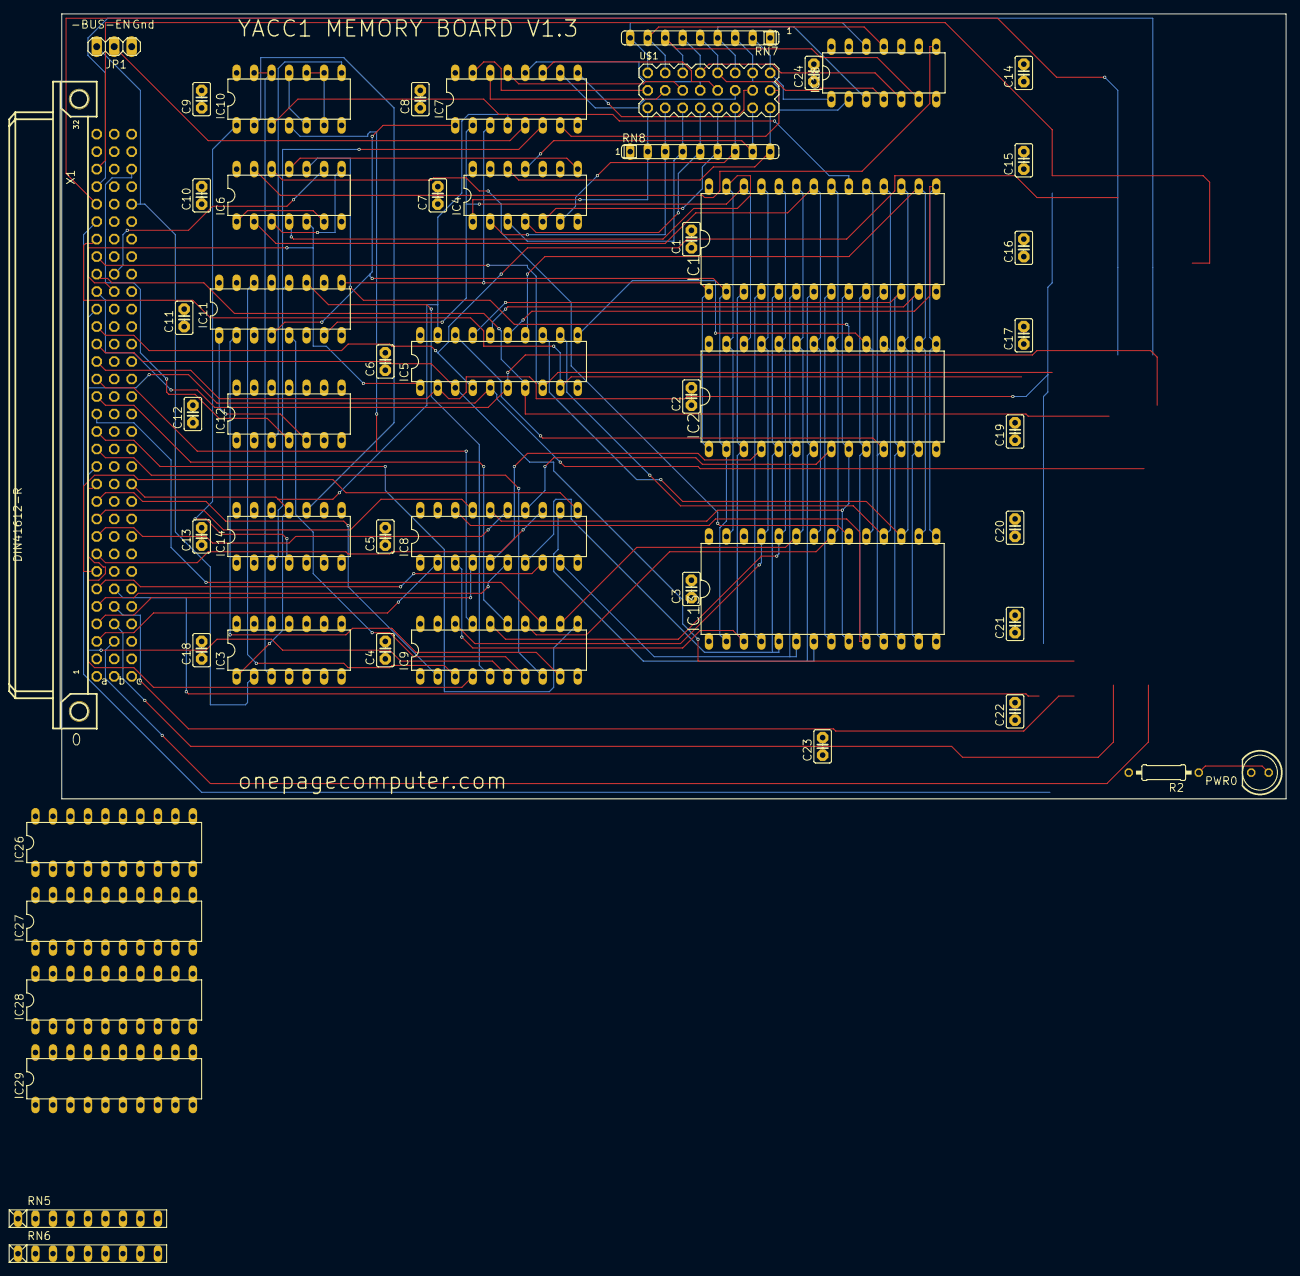
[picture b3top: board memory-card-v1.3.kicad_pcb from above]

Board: 4 copper layers, 177.8 x 114.0 mm, 52 parts (0 on the bottom side), 115 nets.

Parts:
C1, C2, C3, C4, C5, C6, C7, C8, C9, C10, C11, C12, C13, C14, C15, C16, C17, C18, C19, C20, C21, C22, C23, C24: C025-025X050
IC1, IC2, IC13: DIL28-6
IC3: 74LS32N; DIL14
IC4, IC18: 74ALS30N; DIL14
IC5: 74LS245N; DIL20
IC6, IC14: 74LS04N; DIL14
IC7: 74LS138N; DIL16
IC8, IC9: 74LS244N; DIL20
IC10: 74ALS00N; DIL14
IC11: 74LS157N; DIL16
IC12: 74LS74N; DIL14
IC26, IC27, IC28, IC29: 74LS374N; DIL20
JP1: 1X03
PWR0: LED5MM
R2: 330; 0207_10
RN5, RN6: RN-9
RN7, RN8: SIL9
U$1: PIN_3X8
X1: FABC96R

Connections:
-BUS-EN: IC3.2, JP1.1, X1.C28
-HI-RAM: IC2.20, IC6.10
-LO-RAM: IC1.20, IC10.3
-MEM-RD: IC5.1, IC6.5, X1.B23
-MEM-WR: IC6.9, X1.B24
-RESET: IC12.4, X1.C30
-ROM-CS: IC6.12, IC13.20
-TMP-REG-LD0: IC14.1, X1.B28
-TMP-REG-LD1: IC14.13, X1.B30
-TMP-REG-RD0: IC26.1, IC27.1, X1.B27
-TMP-REG-RD1: IC28.1, IC29.1, X1.B29
-VMA: IC3.1, IC5.19, IC7.4, IC14.11, X1.C12
ADDR0: IC8.2, X1.A3
ADDR1: IC8.4, X1.A4
ADDR2: IC8.6, X1.A5
ADDR3: IC8.8, X1.A6
ADDR4: IC8.11, X1.A7
ADDR5: IC8.13, X1.A8
ADDR6: IC8.15, X1.A9
ADDR7: IC8.17, X1.A10
ADDR8: IC9.2, X1.A11
ADDR9: IC9.4, X1.A12
ADDR10: IC9.6, X1.A13
ADDR11: IC9.8, X1.A14
ADDR12: IC9.11, X1.A15
ADDR13: IC9.13, X1.A16
ADDR14: IC9.15, X1.A17
ADDR15: IC9.17, IC10.4, X1.A18
BADDR0: IC1.10, IC2.10, IC8.18, IC13.10
BADDR1: IC1.9, IC2.9, IC8.16, IC13.9
BADDR2: IC1.8, IC2.8, IC8.14, IC13.8
BADDR3: IC1.7, IC2.7, IC8.12, IC13.7
BADDR4: IC1.6, IC2.6, IC8.9, IC13.6
BADDR5: IC1.5, IC2.5, IC8.7, IC13.5
BADDR6: IC1.4, IC2.4, IC8.5, IC13.4
BADDR7: IC1.3, IC2.3, IC8.3, IC13.3
BADDR8: IC1.25, IC2.25, IC9.18, IC13.25
BADDR9: IC1.24, IC2.24, IC9.16, IC13.24
BADDR10: IC1.21, IC2.21, IC9.14, IC13.21
BADDR11: IC1.23, IC2.23, IC9.12, IC13.23
BADDR12: IC1.2, IC2.2, IC7.1, IC11.4, IC13.2
BADDR13: IC1.26, IC2.26, IC7.2, IC11.7
BADDR14: IC1.1, IC2.1, IC7.3, IC11.9
BADDR15: IC7.6, IC11.12, IC14.3
BDATA0: IC1.11, IC2.11, IC5.18, IC13.11
BDATA1: IC1.12, IC2.12, IC5.17, IC13.12
BDATA2: IC1.13, IC2.13, IC5.16, IC13.13
BDATA3: IC1.15, IC2.15, IC5.15, IC13.15
BDATA4: IC1.16, IC2.16, IC5.14, IC13.16
BDATA5: IC1.17, IC2.17, IC5.13, IC13.17
BDATA6: IC1.18, IC2.18, IC5.12, IC13.18
BDATA7: IC1.19, IC2.19, IC5.11, IC13.19
DATA0: IC5.2, IC26.2, IC26.3, IC28.2, IC28.3, RN5.2, X1.A19
DATA1: IC5.3, IC26.4, IC26.5, IC28.4, IC28.5, RN5.3, X1.A20
DATA2: IC5.4, IC26.6, IC26.7, IC28.6, IC28.7, RN5.4, X1.A21
DATA3: IC5.5, IC26.8, IC26.9, IC28.8, IC28.9, RN5.5, X1.A22
DATA4: IC5.6, IC26.12, IC26.13, IC28.12, IC28.13, RN5.6, X1.A23
DATA5: IC5.7, IC26.14, IC26.15, IC28.14, IC28.15, RN5.7, X1.A24
DATA6: IC5.8, IC26.16, IC26.17, IC28.16, IC28.17, RN5.8, X1.A25
DATA7: IC5.9, IC26.18, IC26.19, IC28.18, IC28.19, RN5.9, X1.A26
DATA8: IC27.2, IC27.3, IC29.2, IC29.3, RN6.2, X1.A27
DATA9: IC27.4, IC27.5, IC29.4, IC29.5, RN6.3, X1.A28
DATA10: IC27.6, IC27.7, IC29.6, IC29.7, RN6.4, X1.A29
DATA11: IC27.8, IC27.9, IC29.8, IC29.9, RN6.5, X1.A30
DATA12: IC27.12, IC27.13, IC29.12, IC29.13, RN6.6, X1.B3
DATA13: IC27.14, IC27.15, IC29.14, IC29.15, RN6.7, X1.B4
DATA14: IC27.16, IC27.17, IC29.16, IC29.17, RN6.8, X1.B5
DATA15: IC27.18, IC27.19, IC29.18, IC29.19, RN6.9, X1.B6
FORCE-ROM: IC11.1, IC12.5
GND: C1.2, C2.2, C3.2, C4.2, C5.2, C6.2, C7.2, C8.2, C9.2, C10.2, C11.2, C12.2, C13.2, C14.2, C15.2, C16.2, C17.2, C18.2, C19.1, C20.1, C21.1, C22.1, C23.1, C24.1, IC1.14, IC2.14, IC3.4, IC3.5, IC3.7, IC3.9, IC3.10, IC3.12, IC3.13, IC4.7, IC5.10, IC6.7, IC7.8, IC8.1, IC8.10, IC8.19, IC9.1, IC9.10, IC9.19, IC10.7, IC11.8, IC11.15, IC12.2, IC12.7, IC12.10, IC12.11, IC12.12, IC12.13, IC13.14, IC14.7, IC18.7, IC26.10, IC27.10, IC28.10, IC29.10, JP1.3, PWR0.K, RN5.1, RN6.1, X1.A1, X1.A32, X1.B1, X1.B32, X1.C1, X1.C32
MEM-RD: IC6.1, IC6.6
unnamed: IC6.13, IC18.8
unnamed: IC6.3, IC6.8
unnamed: IC1.22, IC2.22, IC6.2, IC13.22
unnamed: IC1.27, IC2.27, IC6.4, IC13.27
unnamed: IC4.1, RN8.2, U$1.17
unnamed: IC4.2, RN8.3, U$1.18
unnamed: IC4.3, RN8.4, U$1.19
unnamed: IC4.4, RN8.5, U$1.20
unnamed: IC4.5, RN8.6, U$1.21
unnamed: IC4.6, RN8.7, U$1.22
unnamed: PWR0.A, R2.1
unnamed: IC10.2, IC14.10
unnamed: IC10.1, IC14.4
unnamed: IC4.8, IC6.11
unnamed: IC9.9, IC11.2
unnamed: IC9.7, IC11.5
unnamed: IC9.5, IC11.11
unnamed: IC9.3, IC11.14
unnamed: IC10.8, IC12.3
unnamed: IC10.6, IC10.9, IC10.10
unnamed: IC10.5, IC10.11
unnamed: IC7.5, JP1.2
unnamed: IC3.3, IC10.12, IC10.13
unnamed: IC4.11, RN8.8, U$1.23
unnamed: IC4.12, RN8.9, U$1.24
unnamed: IC18.12, RN7.9, U$1.1
unnamed: IC18.11, RN7.8, U$1.2
unnamed: IC18.6, RN7.7, U$1.3
unnamed: IC18.5, RN7.6, U$1.4
unnamed: IC18.1, RN7.2, U$1.8
unnamed: IC14.2, IC26.11, IC27.11
unnamed: IC18.2, RN7.3, U$1.7
unnamed: IC18.3, RN7.4, U$1.6
unnamed: IC7.7, U$1.16
unnamed: IC7.9, U$1.15
unnamed: IC7.10, U$1.14
unnamed: IC7.11, U$1.13
unnamed: IC7.12, U$1.12
unnamed: IC7.13, U$1.11
unnamed: IC7.14, U$1.10
unnamed: IC7.15, U$1.9
unnamed: IC18.4, RN7.5, U$1.5
unnamed: IC14.12, IC28.11, IC29.11
VCC: C1.1, C2.1, C3.1, C4.1, C5.1, C6.1, C7.1, C8.1, C9.1, C10.1, C11.1, C12.1, C13.1, C14.1, C15.1, C16.1, C17.1, C18.1, C19.2, C20.2, C21.2, C22.2, C23.2, C24.2, IC1.28, IC2.28, IC3.14, IC4.14, IC5.20, IC6.14, IC7.16, IC8.20, IC9.20, IC10.14, IC11.3, IC11.6, IC11.10, IC11.13, IC11.16, IC12.1, IC12.14, IC13.28, IC14.14, IC18.14, IC26.20, IC27.20, IC28.20, IC29.20, R2.2, RN7.1, RN8.1, X1.A2, X1.A31, X1.B2, X1.B31, X1.C2, X1.C31

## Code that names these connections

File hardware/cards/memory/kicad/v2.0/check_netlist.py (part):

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  schematic  every part of v1.3 but the REMOVED four (C20-C23, 2026-09-24) is in v2.0; each removed one was on
             v1.3 a capacitor with pin 1 on GND and pin 2 on VCC and nothing else (mem_v2_netlist.removed_pins());
             every net of v1.3 is in v2.0 with the same pins (less the removed caps' pins) and the same name, except that
               - IO-ADDR0-3 / -IO-RD / -IO-WR (v1.3: sheet-1 local labels on X1 only) are global now and ALSO carry
                 the CF section's pins,
               - DATA0-7, -RESET, VCC, GND also carry the CF section's pins,
               - nets KiCad names after a pin (Net-(...)) are compared by their pins only;
             every CF section net (mem_v2_netlist.NETS) is there with exactly its pins (name /Sheet 7/<name>, or the
             shared name); there is no other net; every pin KiCad leaves unconnected is either unconnected on v1.3 or a
             documented CF no-connect, and nothing else is unconnected; every part is v1.3's (same value, footprint)
             or a CF part (value, footprint of cf_netlist.py) or JP3 (rule 7: IC13.27 on ROM-WE with JP3.2, JP3.1
             on the -WE net, JP3.3 on VCC; mem_v2_netlist.wp_apply()) or R15 (rule 8: pin 1 on ADDR15, which must be
             exactly IC10.4, IC9.17, X1.A18 before, pin 2 on GND; mem_v2_netlist.pd_apply()), and nothing else.
  board      every pad of every footprint is on exactly the net the v2.0 schematic gives that pin (same names), the
             pads with no net are exactly the schematic's unconnected pins + the v1.3 pads no schematic pin names
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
